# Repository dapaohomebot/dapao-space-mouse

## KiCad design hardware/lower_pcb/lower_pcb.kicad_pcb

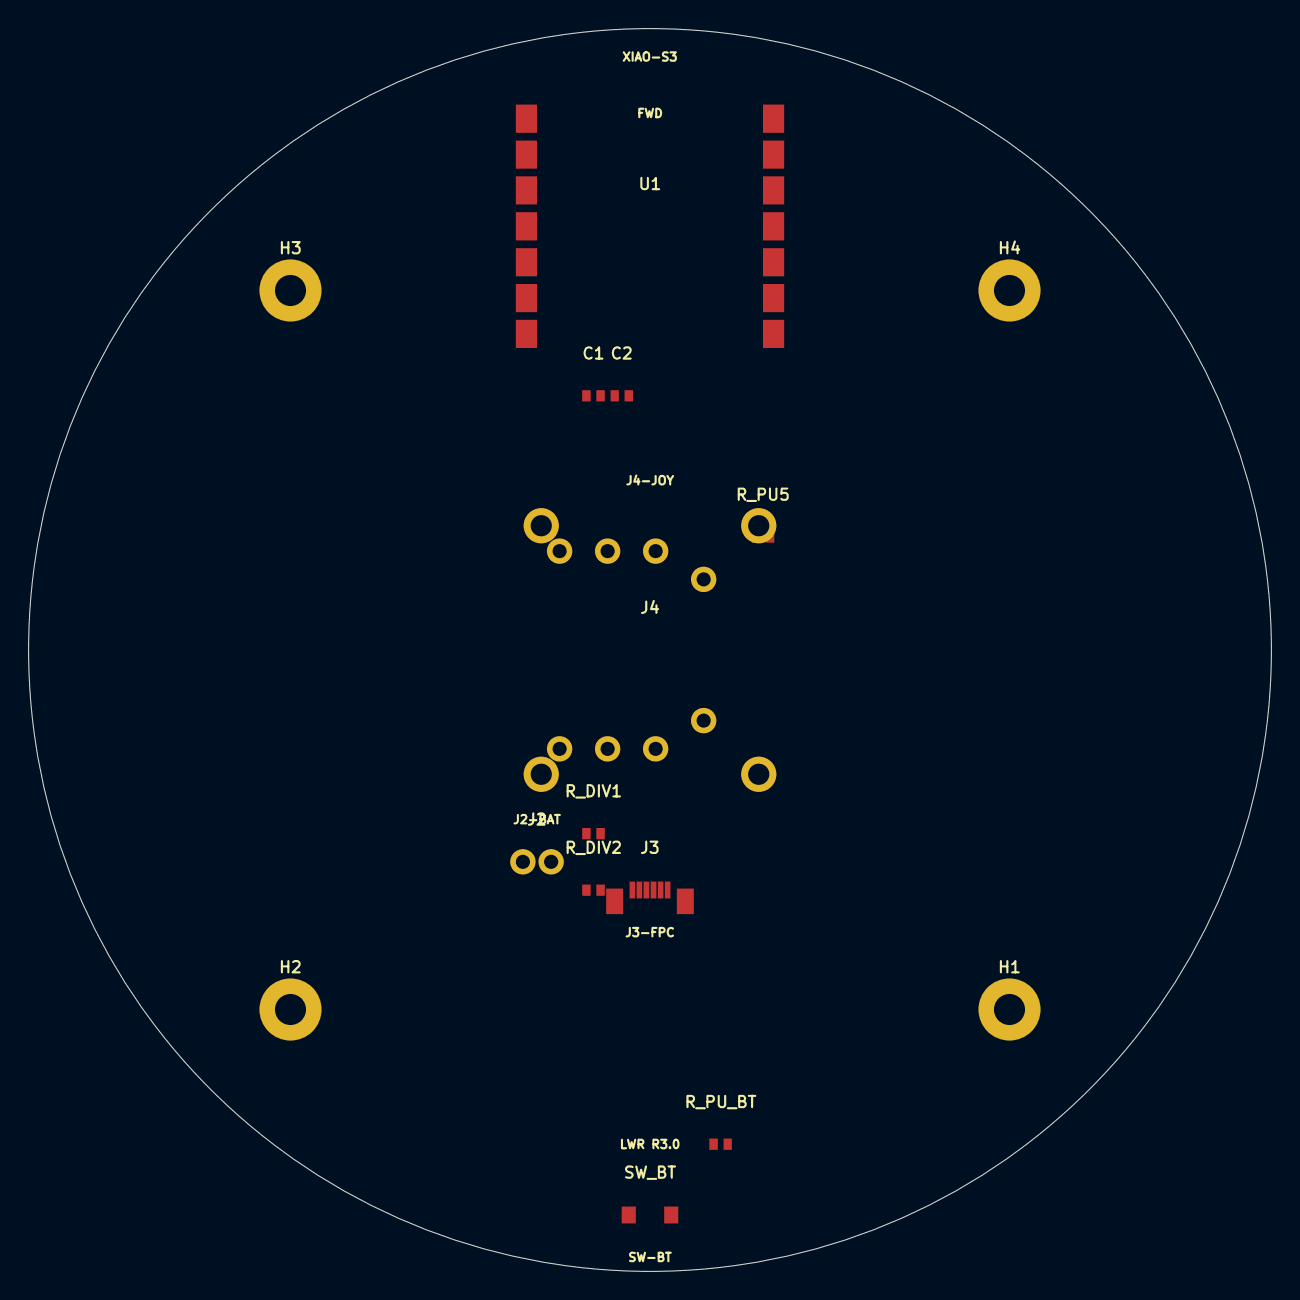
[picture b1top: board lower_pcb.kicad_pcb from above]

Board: 2 copper layers, 88.0 x 88.0 mm, 15 parts (0 on the bottom side), 12 nets, no tracks yet.

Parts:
C1: R-0402; C1
C2: R-0402; C2
H1: M2-Mount; H1
H2: M2-Mount; H2
H3: M2-Mount; H3
H4: M2-Mount; H4
J2: JST-PH-2P; J2
J3: FPC-6P-0.5mm; J3
J4: Alps-RKJXV; J4
R_DIV1: R-0402; R_DIV1
R_DIV2: R-0402; R_DIV2
R_PU5: R-0402; R_PU5
R_PU_BT: R-0402; R_PU_BT
SW_BT: BT-SYNC-SW; SW_BT
U1: Seeed-XIAO-ESP32S3; U1

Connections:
3V3: C1.1, C2.1, J3.1, J4.1, J4.4, R_PU5.1, R_PU_BT.1, U1.14
ADC_BAT: R_DIV1.2, R_DIV2.1, U1.6
BTN_BK: J3.5, U1.9
BTN_FW: J3.6, U1.10
BTN_L: J3.3, U1.7
BTN_R: J3.4, U1.8
BT_SYNC: R_PU_BT.2, SW_BT.1, U1.11
GND: C1.2, C2.2, H1.1, H2.1, H3.1, H4.1, J2.2, J3.2, J3.7, J3.8, J4.3, J4.6, J4.8, J4.M1, J4.M2, J4.M3, J4.M4, R_DIV2.2, SW_BT.2, U1.1, U1.2, U1.12, U1.13, U1.16
JOY_SW: J4.7, R_PU5.2, U1.5
JOY_X: J4.2, U1.3
JOY_Y: J4.5, U1.4
VBAT: J2.1, R_DIV1.1, U1.15

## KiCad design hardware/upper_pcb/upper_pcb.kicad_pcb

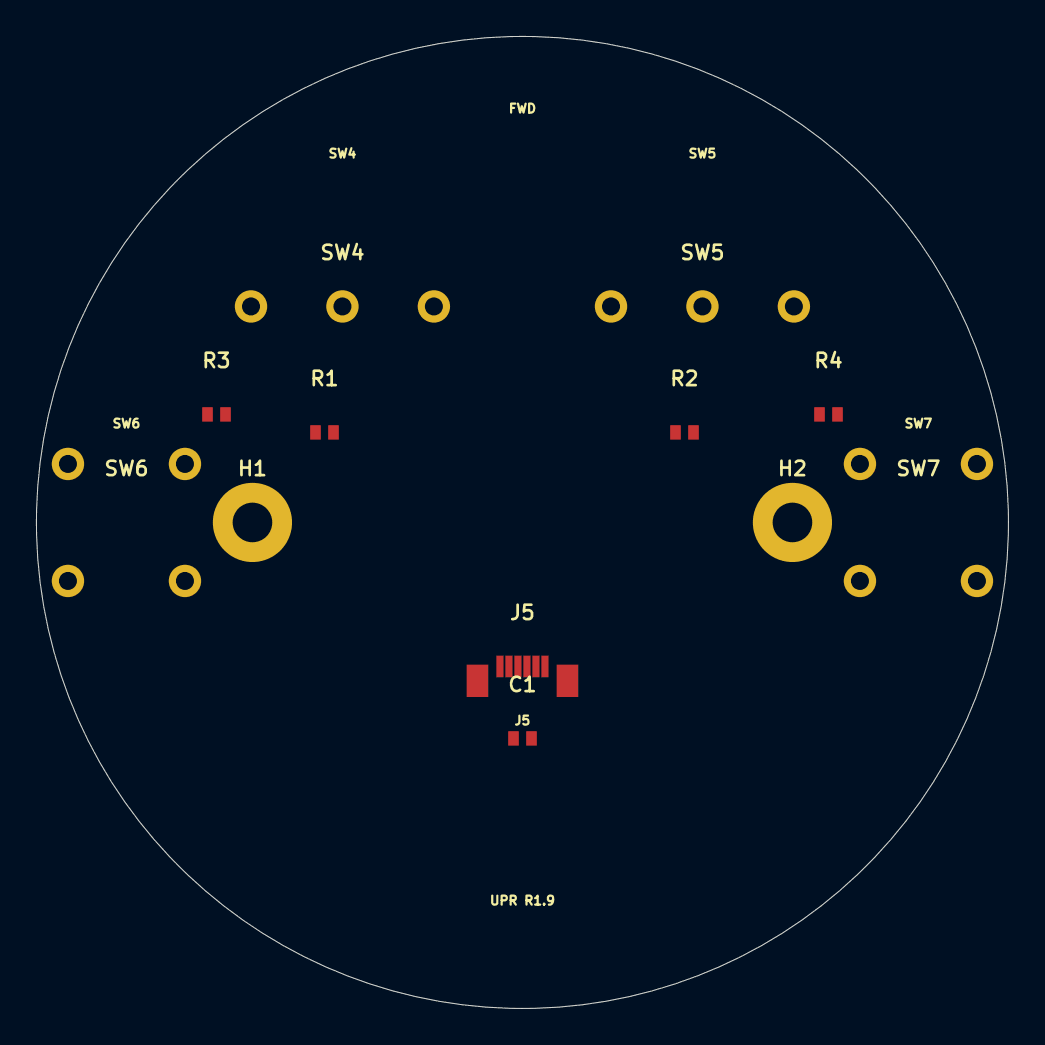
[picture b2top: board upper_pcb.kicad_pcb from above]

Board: 2 copper layers, 54.0 x 54.0 mm, 12 parts (0 on the bottom side), 6 nets, no tracks yet.

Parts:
C1: C-0402; C1
H1: M2-Mount; H1
H2: M2-Mount; H2
J5: FPC-6P-0.5mm; J5
R1: R-0402; R1
R2: R-0402; R2
R3: R-0402; R3
R4: R-0402; R4
SW4: Kailh-GM8.0; SW4
SW5: Kailh-GM8.0; SW5
SW6: Alps-SKHLLBA010; SW6
SW7: Alps-SKHLLBA010; SW7

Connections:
3V3: C1.1, J5.1, R1.1, R2.1, R3.1, R4.1
BTN_BK: J5.5, R3.2, SW6.1
BTN_FW: J5.6, R4.2, SW7.1
BTN_L: J5.3, R1.2, SW4.1
BTN_R: J5.4, R2.2, SW5.1
GND: C1.2, H1.1, H2.1, J5.2, J5.7, J5.8, SW4.2, SW4.3, SW5.2, SW5.3, SW6.2, SW6.3, SW6.4, SW7.2, SW7.3, SW7.4

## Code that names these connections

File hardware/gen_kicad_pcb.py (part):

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  Back pads: GND, VBAT (LiPo positive)

GPIO ASSIGNMENTS:
  D0/A0 (GPIO1)  → JOY_X  (analog)
  D1/A1 (GPIO2)  → JOY_Y  (analog)
  D2/A2 (GPIO3)  → JOY_SW (digital, pull-up)
  D3/A3 (GPIO4)  → ADC_BAT (analog, battery voltage divider)
  D4/SDA (GPIO5) → BTN_L
  D5/SCL (GPIO6) → BTN_R
  D6/TX  (GPIO43)→ BTN_BK
  D7/RX  (GPIO44)→ BTN_FW
  D8/SCK (GPIO7) → BT_SYNC
"""
import math, os

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# ---------------------------------------------------------------
# J3  FPC 6-pin 0.5mm pitch — connects to upper PCB button ring
# ---------------------------------------------------------------
# Pin1=3V3, Pin2=GND, Pin3=BTN_L, Pin4=BTN_R, Pin5=BTN_BK, Pin6=BTN_FW
fpc3_nets = ["3V3","GND","BTN_L","BTN_R","BTN_BK","BTN_FW"]
fpc3_pads = []
for i, net in enumerate(fpc3_nets):
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footprints_upper.append(skhll_fp("SW7", sw7x, sw7y, "BTN_FW"))

# --- J5 FPC 6-pin 0.5mm — connects to lower PCB ---
# Pin1=3V3, Pin2=GND, Pin3=BTN_L, Pin4=BTN_R, Pin5=BTN_BK, Pin6=BTN_FW
fpc5_nets = ["3V3","GND","BTN_L","BTN_R","BTN_BK","BTN_FW"]
fpc5_pads = []
for i, net in enumerate(fpc5_nets):
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
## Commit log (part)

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2026-03-10 Initial project plan: DaPao Space Mouse
    - Development plan with 4 phases (mechanical, PCB, firmware, integration)
    - Bill of materials (~5-17 estimated)
    - Project directory structure
2026-03-10 Update plan for wireless (ESP32-S3 BLE) with all design decisions
    - Wireless BLE via ESP32-S3-WROOM-1 + USB-C charging
    - Off-the-shelf joystick module
    - Scroll via tilt-while-pushed
    - Steel insert weighted base
    - Bare plastic grip
    - LiPo battery + charging circuit
2026-03-10 Add full parametric OpenSCAD 3D model
    - 8 printable parts: base plate, base ring, body shell, top cap,
    4 button caps, joystick coupler
    - Concave hourglass body profile with parametric dimensions
    - Steel insert pockets in base for adjustable weight
    - USB-C port, side button, and power switch cutouts
    - Joystick module mounting with tilt clearance
2026-03-11 v2: Half-circle rocker buttons + side buttons on body
    Major button layout redesign:
    - Top: two half-circle rocker buttons (L/R click) that split the
    circular top, hinged at back, click at front — like a real mouse
    - Side: forward/back buttons moved from base to body shell,
    positioned on left/right sides aligned below the L/R buttons
    - Top frame: new ring + center divider part holds the half-circles
2026-03-11 Remove stale zip, add .gitignore for STL output
2026-03-11 Move side buttons higher on body (55% → 78%)
2026-03-11 Add dual-PCB hardware design (lower + upper board)
    Lower PCB (∅88mm, in base):
    - ESP32-S3-WROOM-1 + USB-C + TP4056 charger + LDO
    - Joystick module (center cutout)
    - FPC connector to upper board
    - Battery connector, power switch, BOOT/RESET
    Upper PCB (∅54mm, in body top):
2026-03-19 feat: split 3D model into individual part files + assembly guide
    - Add case/parts/ directory with one .scad file per printed part
    - Add case/parts/params.scad with all shared parameters & utilities
    - Update case/space_mouse.scad to include from parts/ (assembly only)
    - Add case/ASSEMBLY_GUIDE.md with step-by-step build instructions
    - Update case/README.md with new file structure and usage notes
    Each part file can be opened independently in OpenSCAD and exported
2026-03-19 fix: solid geometry — no floating parts, connected mounting ring, manifold-clean
2026-03-19 fix: align PCB switch/mount positions to case (rev 1.1)
    - SW4/SW5 (L/R click) moved to X=±10mm, Y=+12mm (was ±13.5mm, +10mm)
    - SW6/SW7 (Back/Fwd) confirmed at board edge X=±24mm, Y=0
    - H1/H2 mount holes at X=±15mm, Y=0 (unchanged, now documented)
    - top_frame: switch posts updated to top_sw_x=10, top_sw_offset_y=12
    - top_frame: PCB mount posts at top_mount_x=15, top_mount_y=0
    - top_frame: side cutouts added for SW6/SW7 outward-facing plungers
2026-03-20 docs: add full soldering guide + updated BOM for both PCBs
    - hardware/SOLDERING_GUIDE.md: step-by-step assembly instructions for
    both lower (dia88mm) and upper (dia54mm) PCBs, including component
    order, SMD technique tips, FPC cable wiring, continuity checks,
    and common troubleshooting
    - docs/BOM.md: complete BOM with LCSC part numbers, quantities,
    prices, PCB fab settings for JLCPCB
2026-03-20 chore: update space_mouse.scad include paths for split parts
2026-03-20 feat: add Gerber files for both PCBs (ready for JLCPCB)
2026-03-20 fix: move BTN pull-ups (R1-R4) to upper PCB; update schematics + BOM
    - upper_pcb.kicad_sch rev 1.2: add R1-R4 (10k pull-ups) + C1 (100nF)
    - lower_pcb.kicad_sch rev 1.1: remove R_PU1-R_PU4, keep R_PU5 for JOY_SW
    - docs/BOM.md: updated refs to match new placement
2026-03-20 feat: upgrade upper PCB switches to Kailh GM 8.0 + Blue Dot (rev 1.3)
    - SW4/SW5: Kailh GM 8.0 (3-pin THT, Cherry-style, 12.8x5.8mm)
    plunger UP, pressed by rocker buttons
    - SW6/SW7: Kailh Blue Dot SMT side-button (~8.75mm)
    plunger faces outward L/R through top_frame cutouts
    - R1-R4: 10k pull-ups retained (one per BTN signal, active-low)
    - C1: 100nF decoupling retained
2026-03-20 feat: BT sync button + Blue Dot cutout fix + params update
    - params.scad: top_side_sw_w 9->10mm, top_side_sw_h 5->6mm (Kailh Blue Dot fit)
    - params.scad: add sw_bt_width/height/z/angle for SW_BT cutout
    - base_ring.scad rev 1.1: add SW_BT cutout at 90deg, z=12mm
    - lower_pcb.kicad_sch: SW_BT (GPIO9) + R_PU_BT 10k pull-up documented
    - docs/BOM.md: SW_BT + R_PU_BT added to lower PCB parts list
2026-03-20 feat: updated Gerbers v1.1/v1.3 with GM8.0 THT, Blue Dot SMD, SW_BT cutout
    Lower PCB gerbers v1.1:
    - SW_BT (BT sync) pads added at board edge (90deg, z=12mm)
    - JST-PH J2 battery connector pads (2-pin 2mm pitch)
    - SW1 power switch pads (SPDT 3-pin)
    - Correct XIAO ESP32-S3 castellated pad spacing
    Upper PCB gerbers v1.3:
2026-03-21 feat: lower PCB layout rev 1.3 - joystick centered, XIAO north, FPC south
    Layout changes per design spec:
    - J4 joystick centered at board center (100,100)
    - U1 XIAO ESP32-S3 at north (100,70), USB-C facing north edge
    - J3 FPC at (100,120) - between joystick and south edge
    - M2 mount holes moved to 45/135/225/315 deg R=36mm (clear of components)
    - SW1 power switch west edge, SW_BT south edge
2026-03-21 feat: lower PCB v1.3 - no center hole, full silk labels, complete BOM
    Lower PCB changes:
    - REMOVED 27mm center hole - joystick module mounts on PCB surface
    - Full silkscreen text labels on every component (U1-U4, J1-J5, SW1-SW_BT)
    - GPIO net names on all XIAO pad tick marks (BTN-L/R/BK/FW, JOY-X/Y/SW etc)
    - FPC pin numbers + net names (1:3V3 2:GND 3-6:BTN signals)
    - Battery polarity marks (+/-)
2026-03-21 feat: lower PCB rev 2.0 - remove TP4056/USBLC6, use XIAO onboard charger+ADC
    - REMOVED: U2 TP4056, U4 USBLC6, R5/R6 VBAT divider, R7/R8/R9, LED1/LED2
    - XIAO ESP32-S3 handles LiPo charging (~100mA onboard), USB ESD, charge LED
    - Battery ADC: GPIO10 (ADC_BAT) used directly - onboard voltage divider on XIAO
    - GPIO4 reassigned (freed), GPIO10 = ADC_BAT
    - Silkscreen updated: G10-ADC-BAT label, U2/U4/LED silk removed
    - Simplified BOM: 8 fewer components, ~3 USD savings per unit
2026-03-21 feat: lower PCB v2.1 - Alps RKJXV1224005 direct THT solder (no module/header)
    - Replaced J4 5-pin header + KY-023 module with Alps RKJXV1224005 direct THT footprint
    - 10-pin footprint: 6 signal pins (1.0mm drill) + 4 mounting legs (1.5mm drill)
    - X-axis: CCW=3V3, Wiper=GPIO1, CW=GND
    - Y-axis: CCW=3V3, Wiper=GPIO2, CW=GND
    - SW: GPIO3 + GND (R_PU5 10k pull-up to 3V3)
    - Mounting legs tied to GND pour
2026-03-22 feat: improved silkscreen readability on both PCBs
    Label hierarchy applied consistently:
    - REF designators: scale 0.50 (largest, most important)
    - Component names: scale 0.36 (readable at arm's length)
    - Net/pin labels: scale 0.22 (smallest, for close inspection)
    Lower PCB v2.2:
    - Shorter net abbreviations: BTN-L/R/BK/FW, BT-SYN, ADC-BAT
2026-03-22 feat: move J2 battery to south edge (lower PCB), J5 FPC to south edge (upper PCB)
    Lower PCB v2.3:
    - J2 JST-PH battery connector moved to south board edge (left of center)
    - SW_BT moved to south edge (right of center, beside J2)
    - J3 FPC pulled up slightly to stay between joystick and battery row
    Upper PCB v1.5:
    - J5 FPC moved to south edge of board (Y=122, near board edge at R=27mm)
2026-03-22 feat: J2 battery on B.Cu (lower PCB underside), J5 FPC on B.Cu (upper PCB underside)
    Lower PCB v2.4:
    - J2 JST-PH moved to B.Cu — battery connector on physical underside of board
    - B.SilkS added with J2 label, +/- polarity, BOTTOM MOUNT note
    - J2 drill holes still PTH (accessible from both sides)
    Upper PCB v1.6:
    - J5 FPC moved to B.Cu — ribbon exits from physical underside toward lower PCB
2026-03-22 feat: KiCad PCB files with full netlist and copper traces
    lower_pcb.kicad_pcb (rev 2.4):
    - All pads with correct net assignments
    - 91 trace segments/vias covering all nets:
    3V3 rail, GND pour taps, VBUS, BAT_PLUS, SW_OUT (LDO)
    JOY_X/Y/SW from XIAO to Alps RKJXV pads
    BTN_L/R/BK/FW from XIAO to FPC J3 pins
2026-03-22 fix: use # instead of ; for KiCad S-expression comments
2026-03-23 feat: simplify to 2-layer single-sided routing, all traces on F.Cu
    - All signal and power traces moved to F.Cu only
    - No vias anywhere - eliminates layer-change complexity
    - B.Cu = solid GND pour only (add zone fill in KiCad)
    - BAT_PLUS routed on F.Cu around south edge to SW1
    - J2 battery and J5 FPC connectors both on F.Cu (THT accessible both sides)
    - Lower PCB: 88 segments (was 91 with vias/B.Cu traces)
2026-03-23 fix: correct SW4/SW5 GM8.0 footprint - 3 pins horizontal, 5.08mm pitch
    Previous footprint was wrong (Cherry keyboard MX triangle layout).
    Kailh GM 8.0 uses Omron D2FC-F-7N standard footprint:
    NO(-5.08,0) -- COM(0,0) -- NC(+5.08,0) all on same horizontal axis
    5.08mm (0.2-inch) pin-to-pin pitch
    1.0mm drill, 1.8mm pad diameter
    Updated in:
2026-03-23 feat: replace SW6/SW7 Blue Dot SMD with Alps SKHLLBA010 side-push THT
    - SKHLLBA010: side-push tact switch, 4 THT holes in 6.5x6.5mm square
    - 1.57N actuation (firmer = intentional for Back/Fwd nav buttons)
    - 50k cycle life, DigiKey stocked ~0.53ea, JLCPCB LCSC C115343
    - Footprint: 4x Ø1.0mm holes, 1.8mm pads, signal+GND+2xsnap-in legs
    - Updated: gen_kicad_pcb.py, gen_gerbers.py, add_traces.py
    - Traces: R3/R4 pull-ups repositioned, signal routes to correct hole coords
2026-03-23 fix: rewrite add_traces.py with verified pad coordinates
    All trace endpoints now match exact footprint pad positions:
    - XIAO: 7 left pads + 7 right pads at correct absolute coords
    - J4 Alps RKJXV: X/Y wipers, CCW(3V3), CW(GND), SW, mounting legs
    - J3/J5 FPC: 6 signal pads at 0.5mm pitch
    - U3 LDO SOT-23-5: pin1-5 exact positions
    - J2 JST-PH: pin1(BAT+), pin2(GND)
2026-03-23 feat: replace generic XIAO with Seeed XIAO ESP32-S3 Sense footprint
    - Correct castellated pad pitch: 2.54mm (was wrong 3.0mm)
    - Correct pin count: 8 per side (was 7)
    - GPIO remapping to actual XIAO ESP32-S3 Sense pin names:
    JOY_X → D0/A0 (GPIO1)
    JOY_Y → D1/A1 (GPIO2)
    JOY_SW → D2/A2 (GPIO3)
2026-03-23 feat: replace generic XIAO with Seeed XIAO ESP32-S3 (Sense) lower PCB rev 3.0
    - Seeed XIAO ESP32-S3 has built-in: USB-C, 3V3 LDO (1A), LiPo charger (SGM40567),
    BOOT and RESET buttons — removed external J1 USB-C, U3 LDO, SW1 power switch
    - Correct 7-pad castellated footprint: 2.54mm pitch (not 3.0mm), 1.5x2.0mm pads
    - XIAO pinout per Seeed wiki: L1-L7 and R1-R7, VBAT/GND back pads
    - GPIO assignments: D0-D4(left) for JOY+ADC+BTN_L; D5-D8(right) for BTN_R/BK/FW+BT_SYNC
    - LiPo J2 JST-PH routes directly to XIAO VBAT back pad
2026-03-23 feat: remove all traces (manual routing) + shrink silk labels
    - add_traces.py is now a no-op — route in KiCad manually
    - Lower PCB silk: all labels 0.6mm, shortened to fit within R44mm circle
    - Upper PCB silk: all labels 0.5mm, shortened to fit within R27mm circle
    - No functional changes to footprints or netlist
